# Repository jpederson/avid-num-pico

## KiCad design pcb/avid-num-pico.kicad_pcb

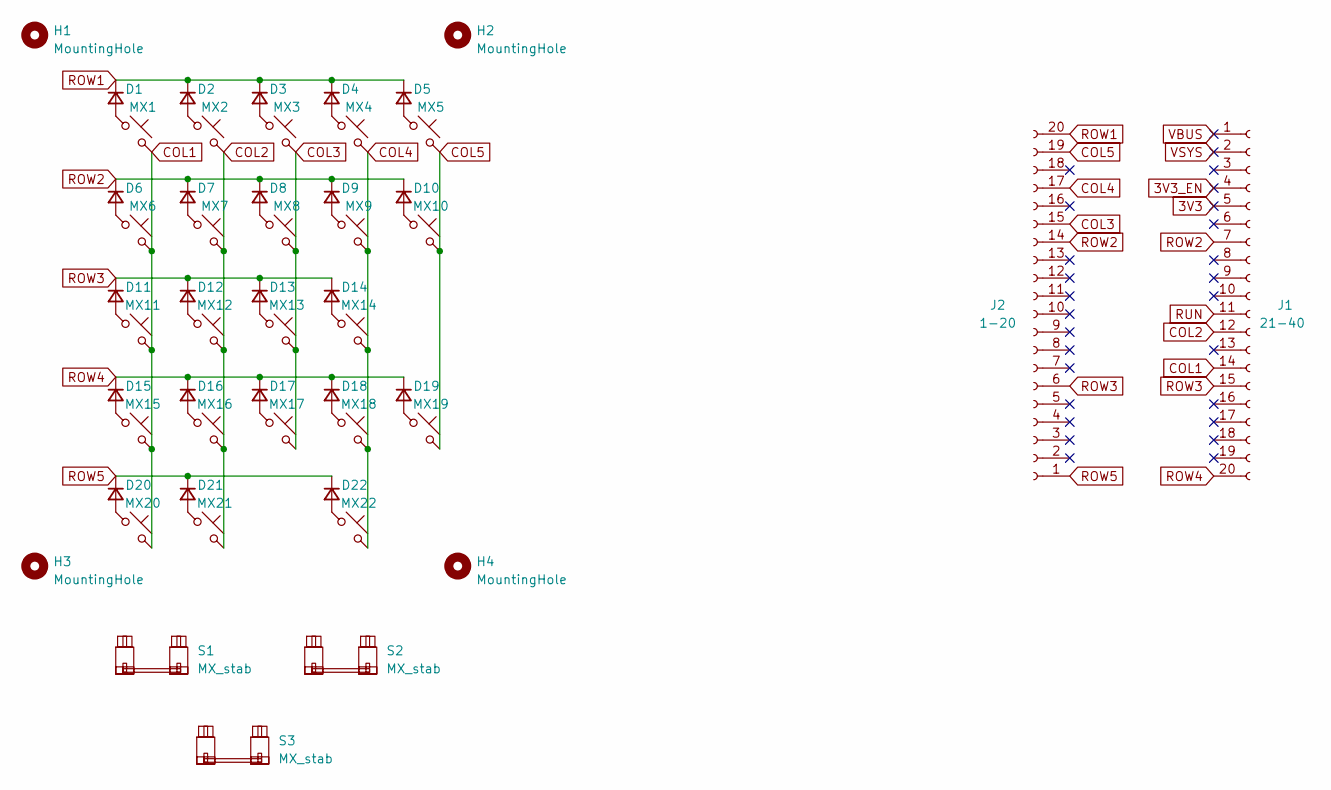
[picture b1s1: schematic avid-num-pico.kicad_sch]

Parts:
D1, D2, D3, D4, D5, D6, D7, D8, D9, D10, D11, D12, D13, D14, D15, D16, D17, D18, D19, D20, D21, D22: D_Small; D_SOD-123F; LCSC Part # C64898
H1, H2, H3, H4: MountingHole; MountingHole_2.7mm_M2.5
J1: 21-40; PinSocket_1x20_P2.54mm_Vertical
J2: 1-20; PinSocket_1x20_P2.54mm_Vertical
MX1, MX2, MX3, MX4, MX5, MX6, MX7, MX8, MX9, MX10, MX11, MX12, MX13, MX14, MX15, MX16, MX17, MX18, MX19, MX20, MX21, MX22: MX_SW_solder; SW_MX_1u
S1, S2, S3: MX_stab; STAB_MX_2u

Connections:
3V3: J1.5
3V3_EN: J1.4
COL1: J1.14, MX1.2, MX6.2, MX11.2, MX15.2, MX20.2
COL2: J1.12, MX2.2, MX7.2, MX12.2, MX16.2, MX21.2
COL3: J2.15, MX3.2, MX8.2, MX13.2, MX17.2
COL4: J2.17, MX4.2, MX9.2, MX14.2, MX18.2, MX22.2
COL5: J2.19, MX5.2, MX10.2, MX19.2
unnamed: D1.2 (A), MX1.1
unnamed: D2.2 (A), MX2.1
unnamed: D3.2 (A), MX3.1
unnamed: D4.2 (A), MX4.1
unnamed: D5.2 (A), MX5.1
unnamed: D6.2 (A), MX6.1
unnamed: D7.2 (A), MX7.1
unnamed: D8.2 (A), MX8.1
unnamed: D9.2 (A), MX9.1
unnamed: D10.2 (A), MX10.1
unnamed: D11.2 (A), MX11.1
unnamed: D12.2 (A), MX12.1
unnamed: D13.2 (A), MX13.1
unnamed: D14.2 (A), MX14.1
unnamed: D15.2 (A), MX15.1
unnamed: D16.2 (A), MX16.1
unnamed: D17.2 (A), MX17.1
unnamed: D18.2 (A), MX18.1
unnamed: D19.2 (A), MX19.1
unnamed: D20.2 (A), MX20.1
unnamed: D21.2 (A), MX21.1
unnamed: D22.2 (A), MX22.1
ROW1: D1.1 (K), D2.1 (K), D3.1 (K), D4.1 (K), D5.1 (K), J2.20
ROW2: D6.1 (K), D7.1 (K), D8.1 (K), D9.1 (K), D10.1 (K), J1.7, J2.14
ROW3: D11.1 (K), D12.1 (K), D13.1 (K), D14.1 (K), J1.15, J2.6
ROW4: D15.1 (K), D16.1 (K), D17.1 (K), D18.1 (K), D19.1 (K), J1.20
ROW5: D20.1 (K), D21.1 (K), D22.1 (K), J2.1
RUN: J1.11
VBUS: J1.1
VSYS: J1.2

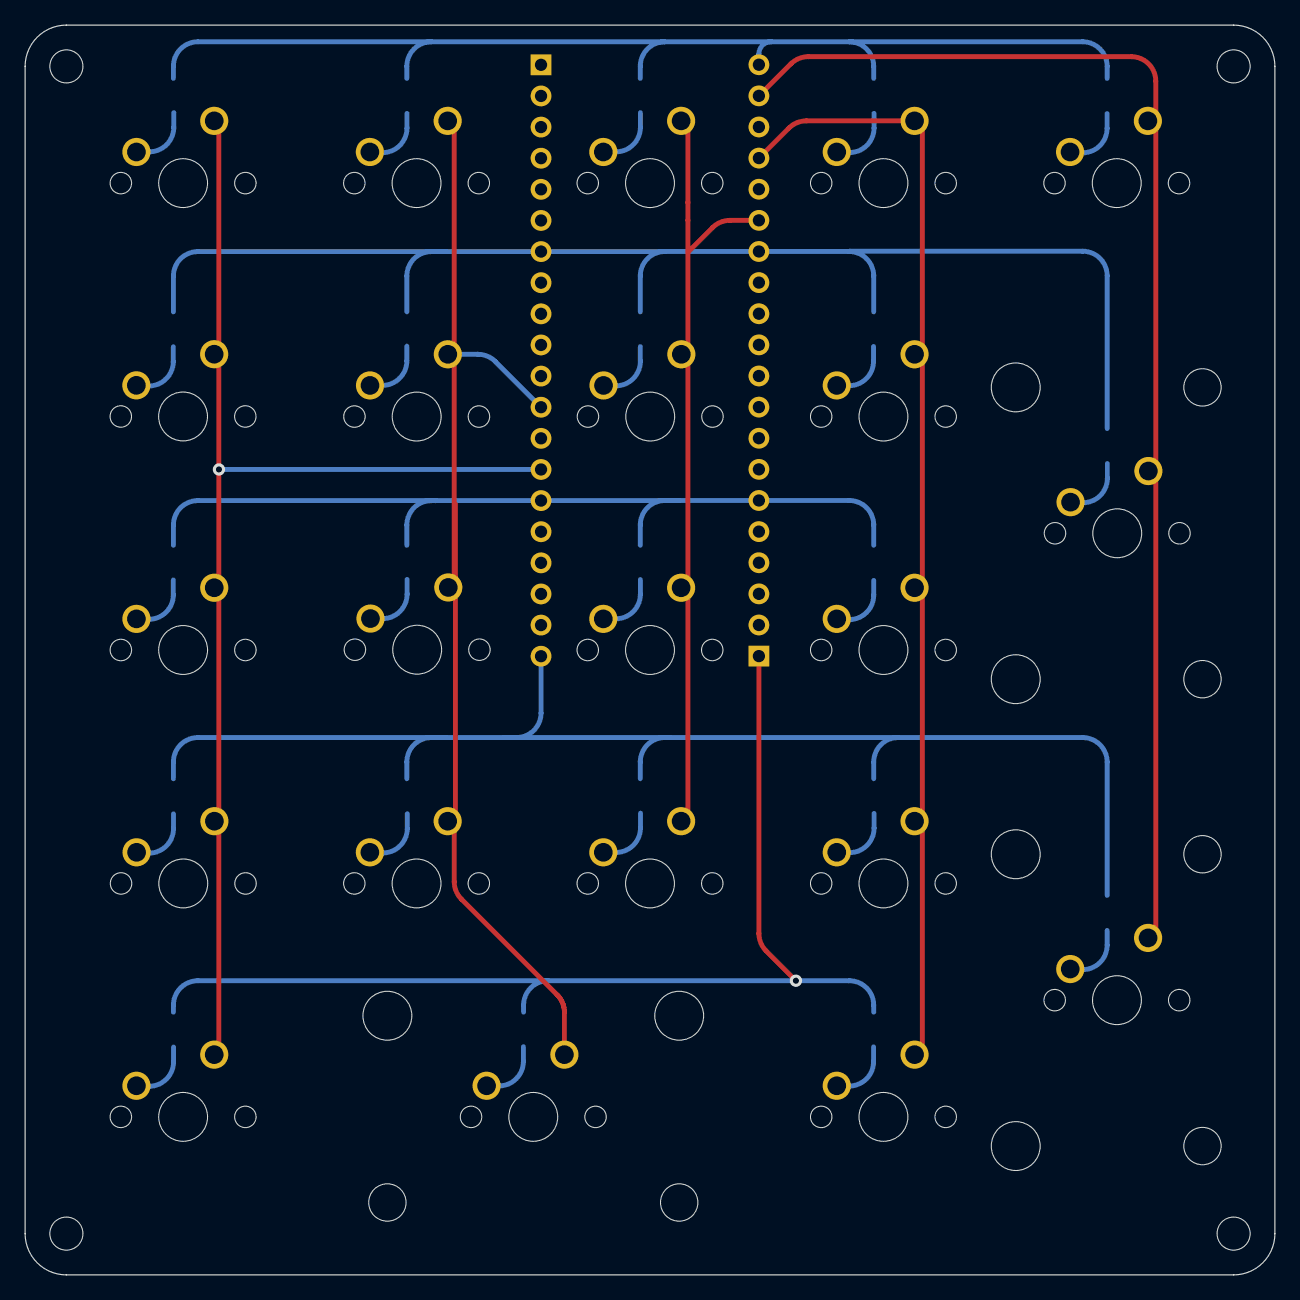
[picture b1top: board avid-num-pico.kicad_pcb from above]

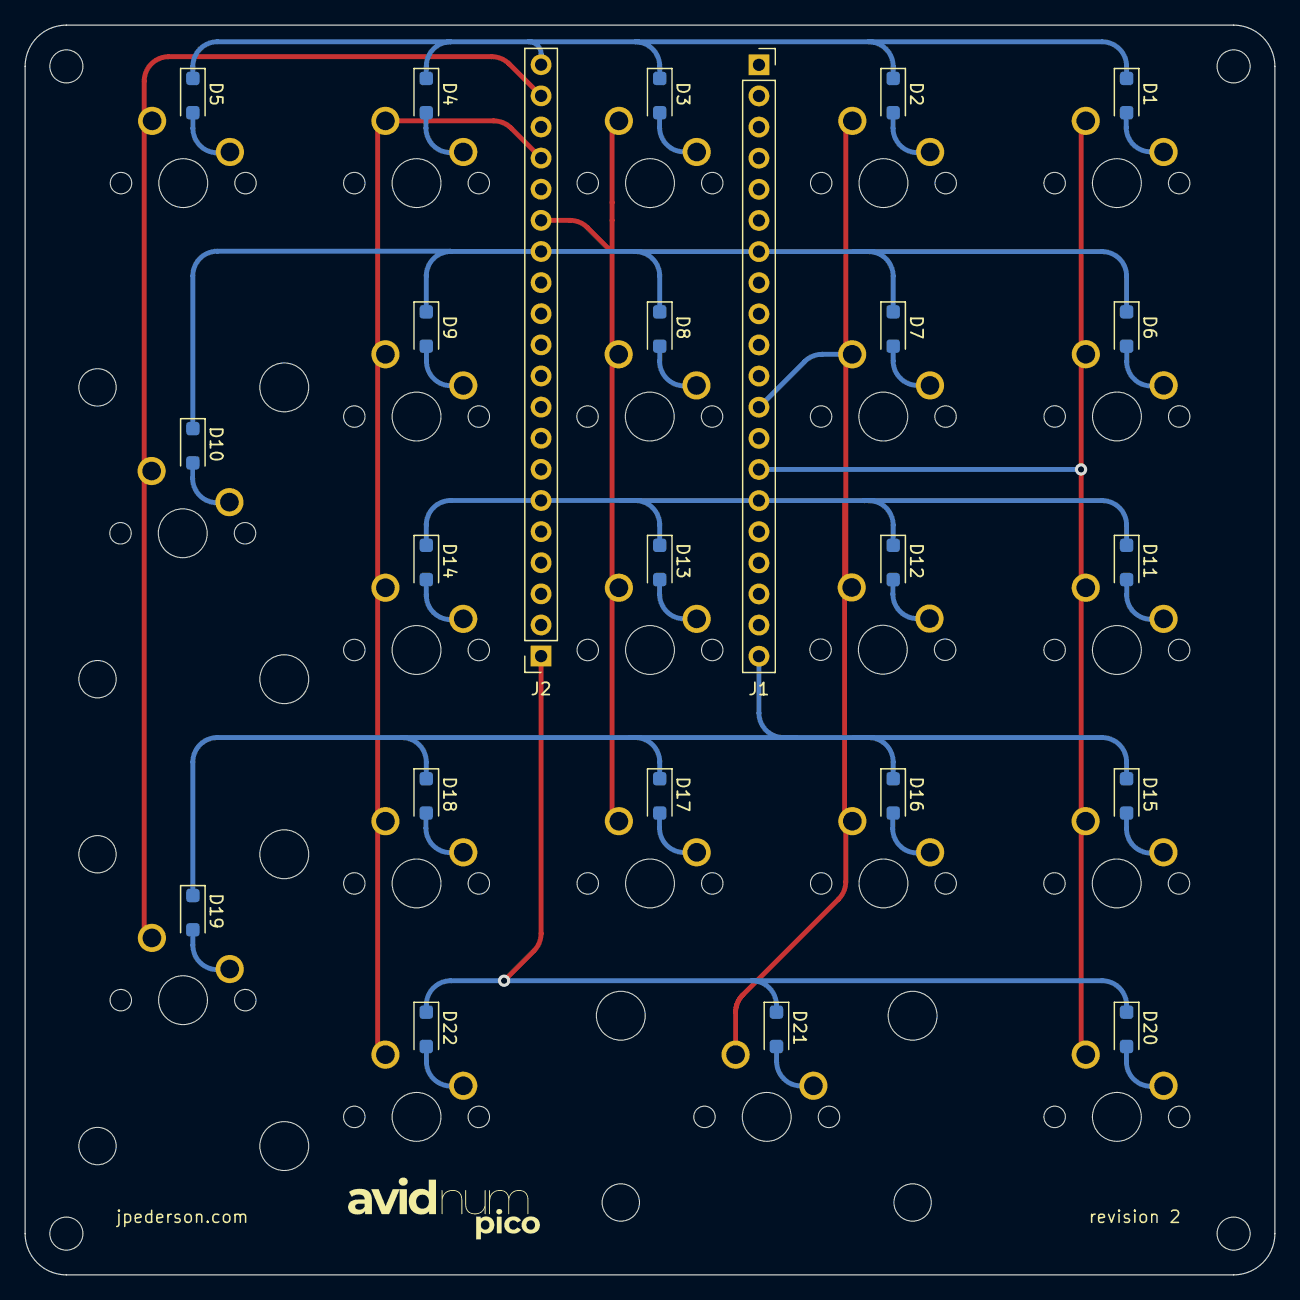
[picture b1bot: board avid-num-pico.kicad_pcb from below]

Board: 2 copper layers, 102.0 x 102.0 mm, 53 parts (24 on the bottom side), 32 nets.

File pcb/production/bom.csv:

"#","Reference","Qty","Value","Footprint","DNP"
"1","D1, D2, D3, D4, D5, D6, D7, D8, D9, D10, D11, D12, D13, D14, D15, D16, D17, D18, D19, D20, D21, D22","22","D_Small","Diode_SMD:D_SOD-123F",""
"2","H1, H2, H3, H4","4","MountingHole","MountingHole:MountingHole_2.7mm_M2.5",""
"3","J1","1","21-40","Connector_PinSocket_2.54mm:PinSocket_1x20_P2.54mm_Vertical",""
"4","J2","1","1-20","Connector_PinSocket_2.54mm:PinSocket_1x20_P2.54mm_Vertical",""
"5","MX1, MX2, MX3, MX4, MX5, MX6, MX7, MX8, MX9, MX10, MX11, MX12, MX13, MX14, MX15, MX16, MX17, MX18, MX19, MX20, MX21, MX22","22","MX_SW_solder","marbastlib-mx:SW_MX_1u",""
"6","S1, S2, S3","3","MX_stab","marbastlib-mx:STAB_MX_2u",""

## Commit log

2023-06-08 Initial commit.
